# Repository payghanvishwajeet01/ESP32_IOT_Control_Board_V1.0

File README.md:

The ESP32_IOT_Control_Board_V1.0 is a compact, ESP32-based control board designed for smart home and industrial automation applications. 
It integrates Wi-Fi and BLE connectivity, enabling seamless cloud and local communication. 
The board features 4-channel relay outputs for reliable control of AC and DC loads. 
An onboard flame detection sensor interface enhances safety and monitoring capabilities. 
The power section supports a wide input range (90–264V AC) with onboard regulation for stable 5V and 3.3V outputs. 
Auto-reset and auto-boot circuitry simplify firmware uploading and development. 
Built-in protection components such as polyfuse, TVS diodes, and flyback diodes improve reliability. 
User-programmable status and relay LEDs provide real-time visual feedback. Multiple GPIO, UART, and I²C interfaces allow easy expansion with external sensors and modules. 
Overall, the board is optimized for robust, scalable, and production-ready IoT solutions.
# ESP32_IoT_Control_Board_V1.0

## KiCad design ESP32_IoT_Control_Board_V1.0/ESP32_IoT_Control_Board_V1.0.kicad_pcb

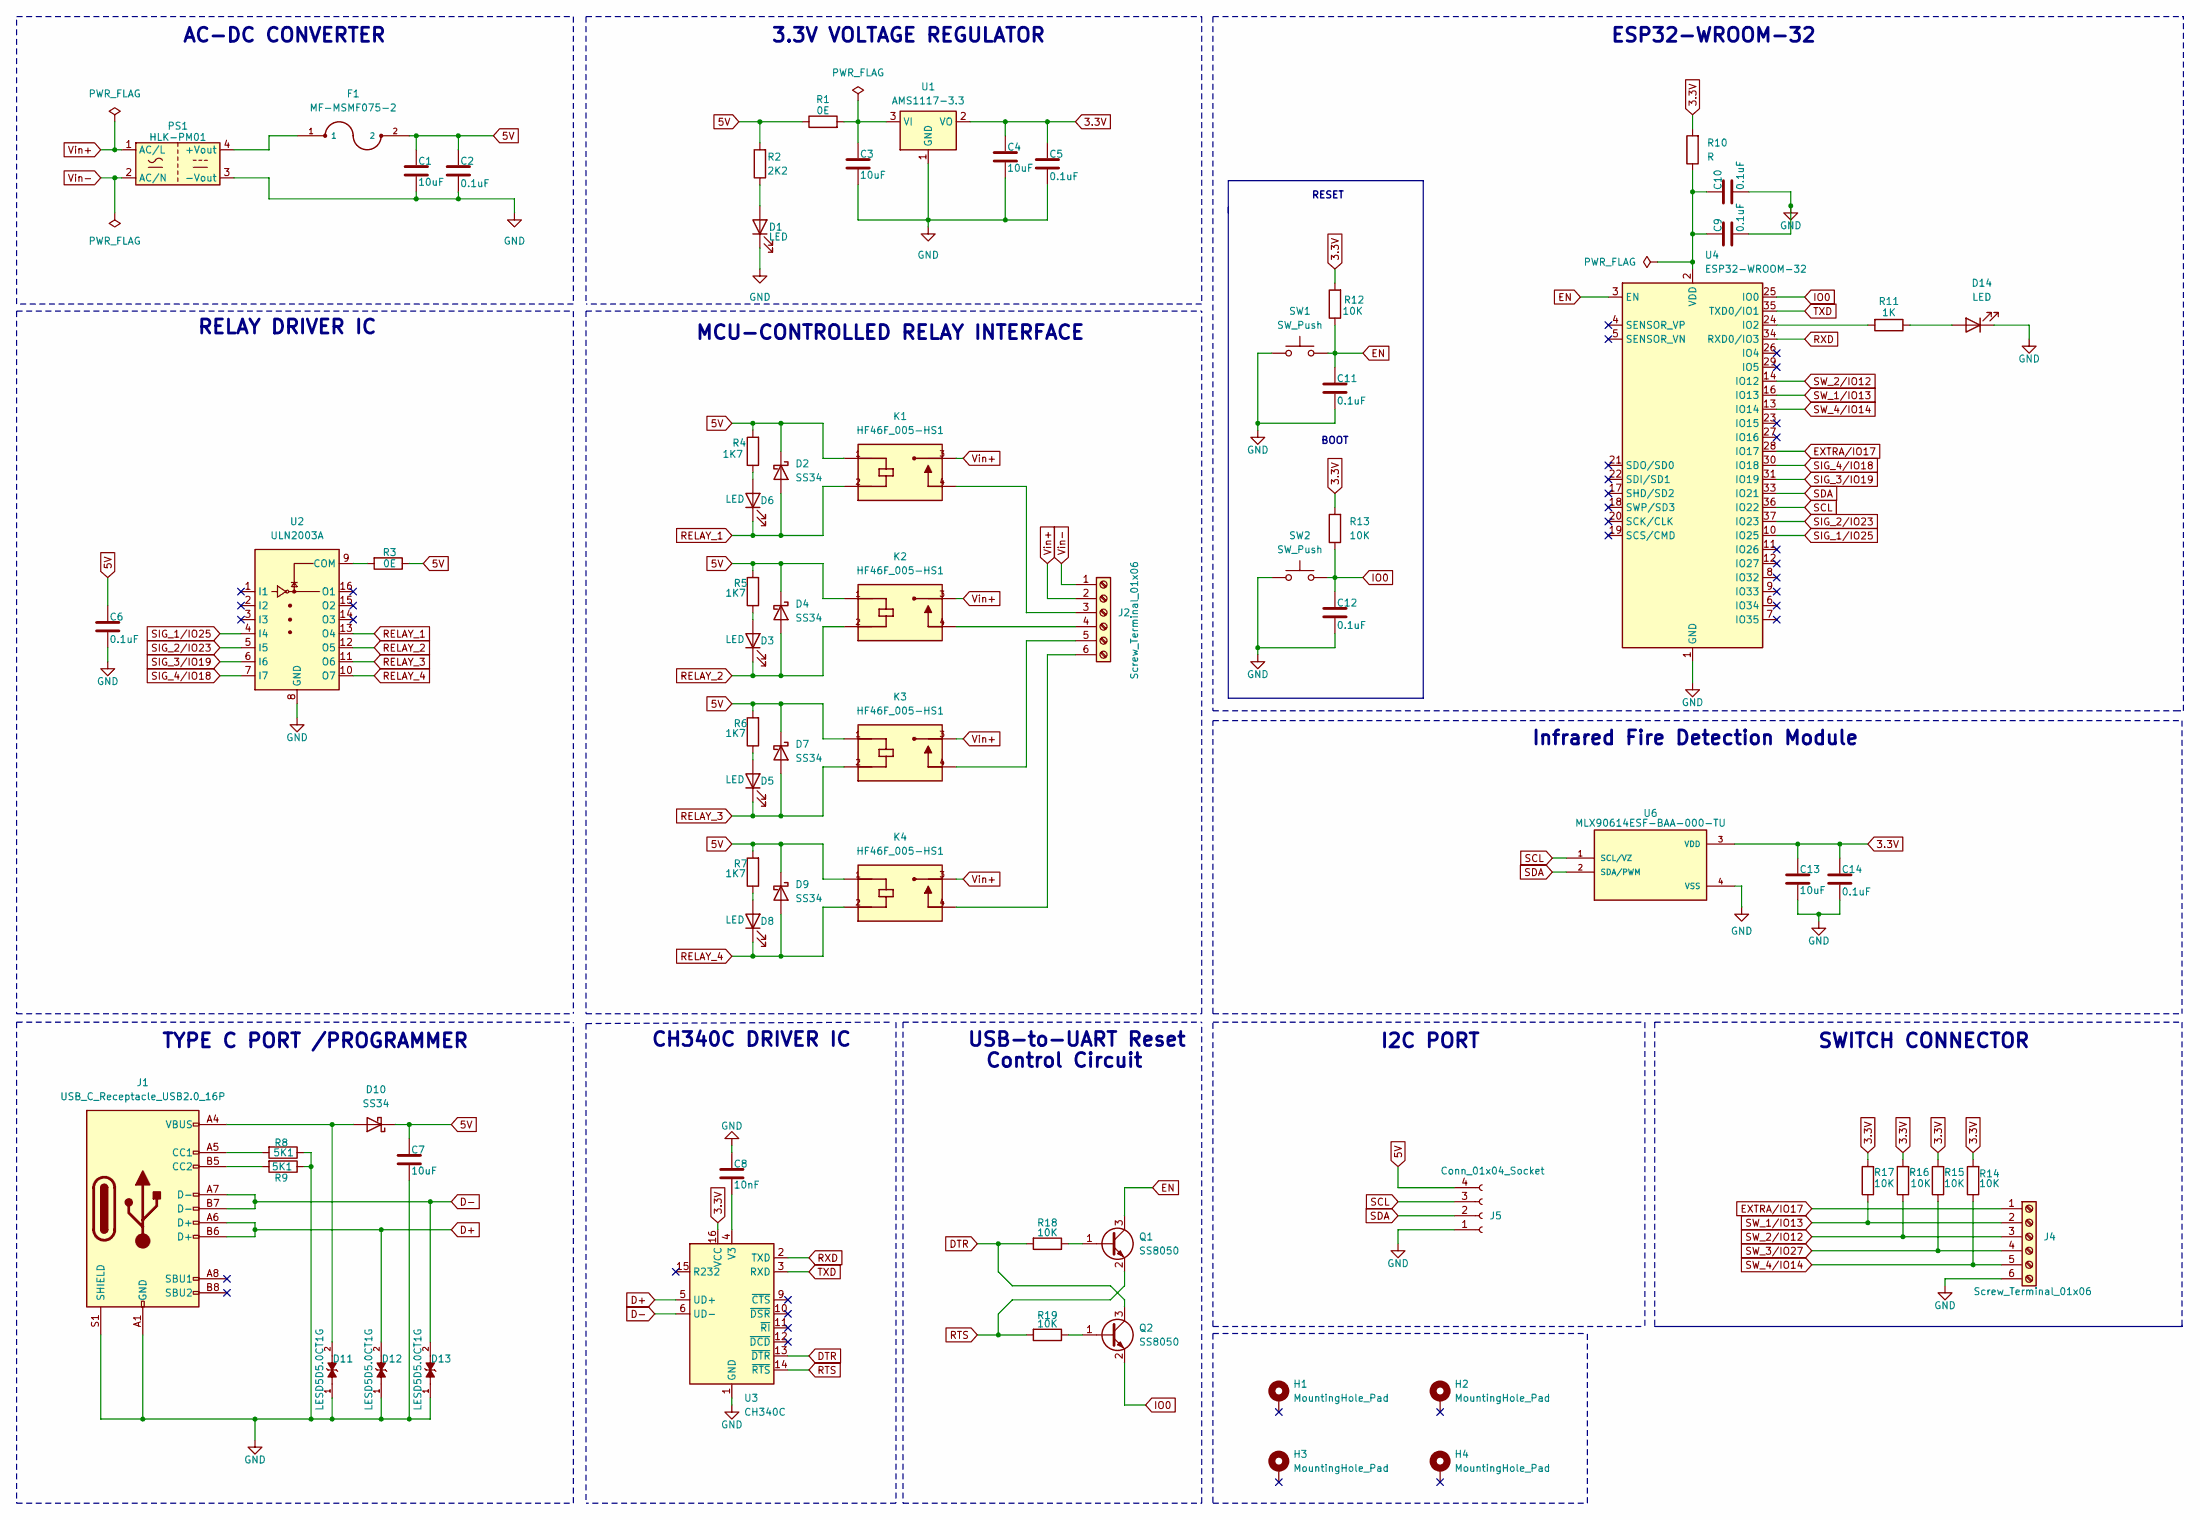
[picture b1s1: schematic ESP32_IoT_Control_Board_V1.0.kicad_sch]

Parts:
C1, C3, C4, C7, C13: 10uF; C_0805_2012Metric
C2, C5, C6, C9, C10, C11, C12, C14: 0.1uF; C_0603_1608Metric
C8: 10nF; C_0603_1608Metric
D1, D3, D5, D6, D8, D14: LED; LED_0603_1608Metric
D2, D4, D7, D9, D10: SS34; D_SMA
D11, D12, D13: LESD5D5.0CT1G; TVS_LESD5D5.0CT1G; PARTREV O
F1: MF-MSMF075-2; FUSM4632X85
H1, H2, H3, H4: MountingHole_Pad; MountingHole_2.5mm_Pad_Via
J1: USB_C_Receptacle_USB2.0_16P; AMPHENOL_12402012E212A
J2, J4: Screw_Terminal_01x06; TerminalBlock_MaiXu_MX126-5.0-06P_1x06_P5.00mm
J5: Conn_01x04_Socket; PinSocket_1x04_P2.54mm_Vertical
K1, K2, K3, K4: HF46F_005-HS1; RELAY_HF46F_005-HS1; PARTREV 1.00
PS1: HLK-PM01; Converter_ACDC_Hi-Link_HLK-PMxx
Q1, Q2: SS8050; SOT-23
R1, R3: 0E; R_0603_1608Metric
R2: 2K2; R_0603_1608Metric
R4, R5, R6, R7: 1K7; R_0603_1608Metric
R8, R9: 5K1; R_0603_1608Metric
R10: R; R_0603_1608Metric
R11: 1K; R_0603_1608Metric
R12, R13, R14, R15, R16, R17, R18, R19: 10K; R_0603_1608Metric
SW1, SW2: SW_Push; SW_SKRPABE010
U1: AMS1117-3.3; SOT-223-3_TabPin2
U2: ULN2003A; SOIC127P600X175-16N
U3: CH340C; SOIC-16_3.9x9.9mm_P1.27mm
U4: ESP32-WROOM-32
U6: MLX90614ESF-BAA-000-TU; TO254P942H425-4; PARTREV 13

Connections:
3.3V: C4.1, C5.1, C13.1, C14.1, R10.2, R12.2, R13.2, R14.2, R15.2, R16.2, R17.2, U1.2 (VO), U3.16 (VCC), U6.3 (VDD)
5V: C1.1, C2.1, C6.1, C7.1, D2.1 (K), D4.1 (K), D7.1 (K), D9.1 (K), D10.1 (K), F1.2, J5.4, K1.1, K2.1, K3.1, K4.1, R1.1, R2.2, R3.1, R4.2, R5.2, R6.2, R7.2
D+: D12.2, J1.A6 (D+), J1.B6 (D+), U3.5 (UD+)
D-: D13.2, J1.A7 (D-), J1.B7 (D-), U3.6 (UD-)
DTR: Q2.3 (C), R18.2, U3.13 (~DTR)
EN: C11.1, Q1.3 (C), R12.1, SW1.2, U4.3 (EN)
EXTRA/IO17: J4.1, U4.28 (IO17)
GND: C1.2, C2.2, C3.2, C4.2, C5.2, C6.2, C7.2, C8.1, C9.2, C10.2, C11.2, C12.2, C13.2, C14.2, D1.1 (K), D11.1, D12.1, D13.1, D14.1 (K), J1.A1 (GND), J1.A12 (GND), J1.B1 (GND), J1.B12 (GND), J1.S1 (SHIELD), J4.6, J5.1, PS1.3 (-Vout), R8.1, R9.1, SW1.1, SW2.1, U1.1 (GND), U2.8 (GND), U3.1 (GND), U4.1 (GND), U4.15 (GND), U4.38 (GND), U4.39 (GND), U6.4 (VSS)
IO0: C12.1, Q2.2 (E), R13.1, SW2.2, U4.25 (IO0)
unnamed: D1.2 (A), R2.1
unnamed: D3.2 (A), R5.1
unnamed: D5.2 (A), R6.1
unnamed: D6.2 (A), R4.1
unnamed: D8.2 (A), R7.1
unnamed: D10.2 (A), D11.2, J1.A4 (VBUS), J1.A9 (VBUS), J1.B4 (VBUS), J1.B9 (VBUS)
unnamed: D14.2 (A), R11.1
unnamed: J1.A5 (CC1), R8.2
unnamed: J1.B5 (CC2), R9.2
unnamed: J2.3, K1.4
unnamed: J2.4, K2.4
unnamed: J2.5, K3.4
unnamed: J2.6, K4.4
unnamed: F1.1, PS1.4 (+Vout)
unnamed: Q1.1 (B), R18.1
unnamed: Q2.1 (B), R19.1
unnamed: C3.1, R1.2, U1.3 (VI)
unnamed: R3.2, U2.9 (COM)
unnamed: C8.2, U3.4 (V3)
unnamed: R11.2, U4.24 (IO2)
unnamed: C9.1, C10.1, R10.1, U4.2 (VDD)
RELAY_1: D2.2 (A), D6.1 (K), K1.2, U2.13 (O4)
RELAY_2: D3.1 (K), D4.2 (A), K2.2, U2.12 (O5)
RELAY_3: D5.1 (K), D7.2 (A), K3.2, U2.11 (O6)
RELAY_4: D8.1 (K), D9.2 (A), K4.2, U2.10 (O7)
RTS: Q1.2 (E), R19.2, U3.14 (~RTS)
RXD: U3.2 (TXD), U4.34 (RXD0/IO3)
SCL: J5.3, U4.36 (IO22), U6.1 (SCL/VZ)
SDA: J5.2, U4.33 (IO21), U6.2 (SDA/PWM)
SIG_1/IO25: U2.4 (I4), U4.10 (IO25)
SIG_2/IO23: U2.5 (I5), U4.37 (IO23)
SIG_3/IO19: U2.6 (I6), U4.31 (IO19)
SIG_4/IO18: U2.7 (I7), U4.30 (IO18)
SW_1/IO13: J4.2, R17.1, U4.16 (IO13)
SW_2/IO12: J4.3, R16.1, U4.14 (IO12)
SW_3/IO27: J4.4, R15.1
SW_4/IO14: J4.5, R14.1, U4.13 (IO14)
TXD: U3.3 (RXD), U4.35 (TXD0/IO1)
Vin+: J2.2, K1.3, K2.3, K3.3, K4.3, PS1.1 (AC/L)
Vin-: J2.1, PS1.2 (AC/N)

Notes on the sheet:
BOOT
RESET
AC-DC CONVERTER
RELAY DRIVER IC
3.3V VOLTAGE REGULATOR
TYPE C PORT /PROGRAMMER
USB-to-UART Reset
I2C PORT
Infrared Fire Detection Module
SWITCH CONNECTOR
CH340C DRIVER IC
ESP32-WROOM-32
Control Circuit
MCU-CONTROLLED RELAY INTERFACE

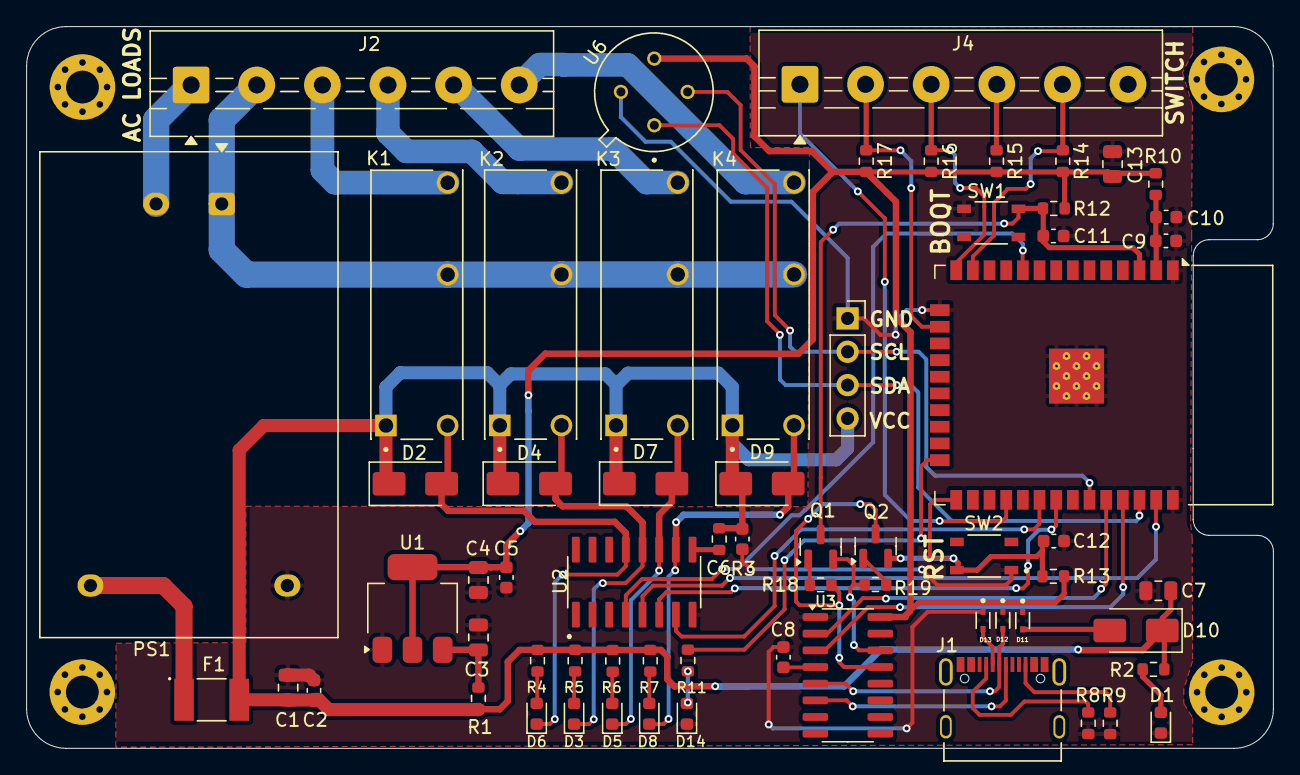
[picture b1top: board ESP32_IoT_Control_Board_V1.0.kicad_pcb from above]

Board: 2 copper layers, 95.0 x 55.0 mm, 70 parts (1 on the bottom side), 49 nets.

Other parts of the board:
QR*****: ESP_IOT
